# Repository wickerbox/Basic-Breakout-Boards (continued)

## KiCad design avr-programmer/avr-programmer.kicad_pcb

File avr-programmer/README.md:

<!--- start title --->
# Atmega328-based AVR Programmer v1.1
Simple Atmega328-based AVR programmer with ISP and FTDI breakout

Updated: 07 March 2017

Author: Jenner Hanni
Website: http://wickerbox.net
Company: Wickerbox Electronics
License: CERN Open Hardware License v1.2

<!--- end title --->
I made it to have a dedicated board containing Nick Gammon's Arduino sketch for bootloading. 

### Bill of Materials

<!--- bom start --->
|Ref|Qty|Description|Digikey PN|
|---|---|-----------|------|
|C2 C3|2|CAP CER 22pF 100V C0G NP0 0603|399-11145-1-ND|
|C4|1|CAP CER 1UF 25V X7R 0603|587-2984-1-ND|
|C5 C6 C1|3|CAP CER 0.1UF 100V X7R 0603|490-3285-1-ND|
|J1|1|HEADER MALE 6POS TH 1x06 0.1”|952-1902-ND|
|J2|1|HEADER MALE 6POS 2x3 0.1”|952-1921-ND|
|R1|1|RES SMD 10K OHM 5% 1/8W 0805|311-10KARCT-ND|
|S1|1|SWITCH TACTILE SPST-NO 0.05A 12V|SW1020CT-ND|
|S2|1|SWITCH SLIDE SPDT 200MA 30V|EG1903-ND|
|U1|1|IC MCU 8BIT 32KB FLASH 32TQFP|ATMEGA328P-AU-ND|
|X1|1|CRYSTAL 16MHz 18pF 40 OHM 4SMD|CTX1206CT-ND|

<!--- bom end --->

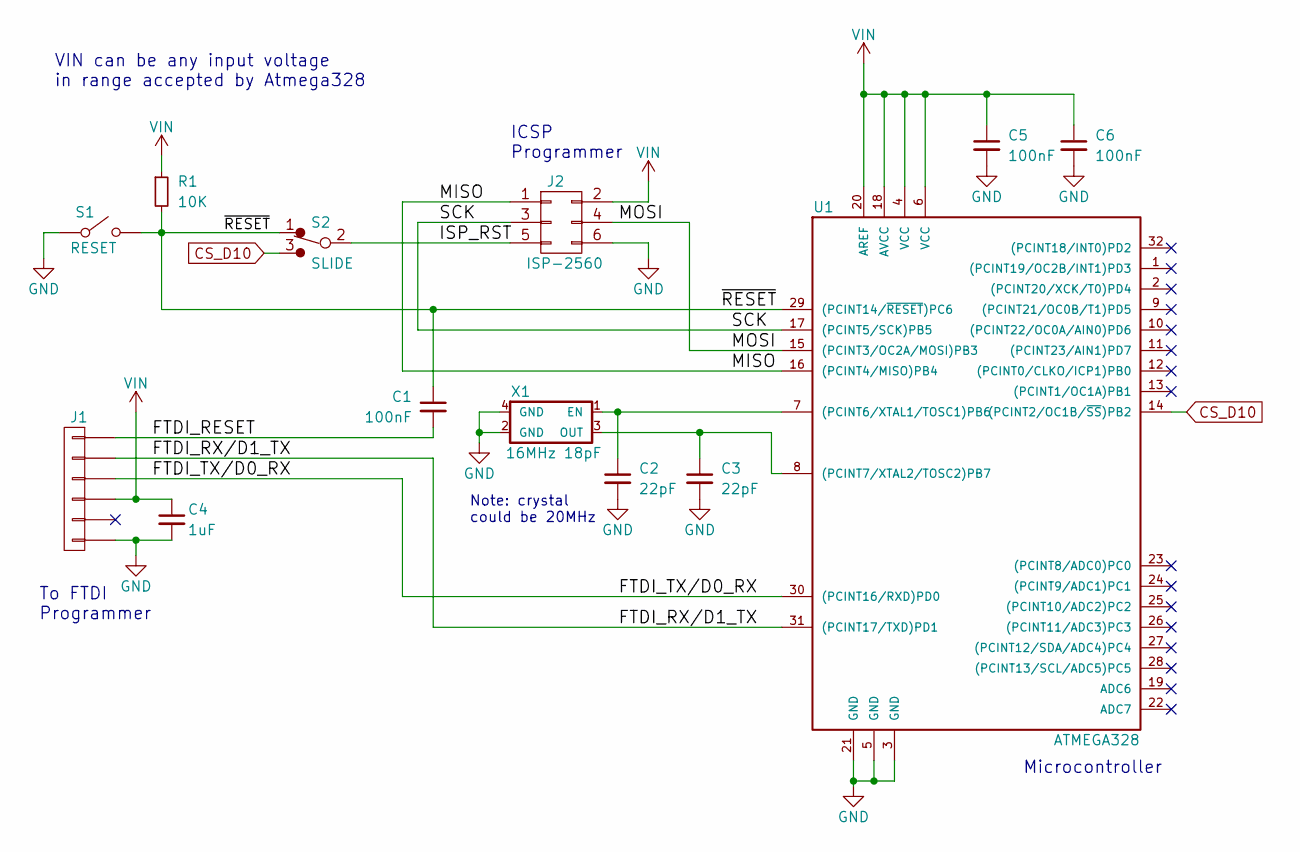
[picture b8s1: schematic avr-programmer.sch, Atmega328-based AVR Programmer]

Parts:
C1, C5, C6: 100nF; RLC-0603-SMD
C2, C3: 22pF; RLC-0603-SMD
C4: 1uF; RLC-0603-SMD
J1: FTDI; CONN-HEADER-STRAIGHT-P2.54MM-1x06
J2: ISP-2560; CONN-HEADER-STRAIGHT-P2.54MM-2x03
R1: 10K; RLC-0805-SMD
S1: RESET; SWITCH-OMRON-MOMENTARY-SMD-B3U-1000P
S2: SLIDE; SWITCH-ESWITCH-SLIDE-TH-EG1218
U1: ATMEGA328; TQFP-32-7x7MM-P0.8MM
X1: 16MHz 18pF; CRYSTAL-CTS-4SMD

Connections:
/FTDI_RESET: C1.2, J1.1
/FTDI_RX/D1_TX: J1.2, U1.31 ((PCINT17/TXD)PD1)
/FTDI_TX/D0_RX: J1.3, U1.30 ((PCINT16/RXD)PD0)
/ISP_RST: J2.5, S2.2
/MISO: J2.1, U1.16 ((PCINT4/MISO)PB4)
/MOSI: J2.4, U1.15 ((PCINT3/OC2A/MOSI)PB3)
/SCK: J2.3, U1.17 ((PCINT5/SCK)PB5)
/~RESET: C1.1, R1.2, S1.2, S2.1, U1.29 ((PCINT14/~RESET~)PC6)
CS_D10: S2.3, U1.14 ((PCINT2/OC1B/~SS~)PB2)
GND: C2.2, C3.2, C4.2, C5.2, C6.2, J1.6, J2.6, S1.1, U1.3 (GND), U1.5 (GND), U1.21 (GND), X1.2 (GND), X1.4 (GND)
unnamed: C2.1, U1.7 ((PCINT6/XTAL1/TOSC1)PB6), X1.1 (EN)
unnamed: C3.1, U1.8 ((PCINT7/XTAL2/TOSC2)PB7), X1.3 (OUT)
VIN: C4.1, C5.1, C6.1, J1.4, J2.2, R1.1, U1.4 (VCC), U1.6 (VCC), U1.18 (AVCC), U1.20 (AREF)

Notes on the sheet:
To FTDI Programmer
ICSP Programmer
VIN can be any input voltage in range accepted by Atmega328
Microcontroller
Note: crystal could be 20MHz

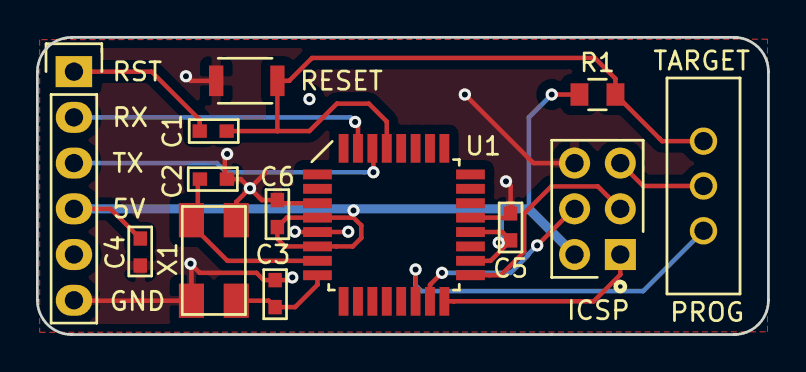
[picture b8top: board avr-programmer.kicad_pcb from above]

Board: 2 copper layers, 40.6 x 16.5 mm, 13 parts (0 on the bottom side), 13 nets.

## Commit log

2016-08-13 Needs major fixes, since board on order doesn't match this after libs update. BOM's OK though.
2016-08-13 Swapped for cheaper capacitors. Updated qty.
2016-08-13 Added project. NOT READY FOR RELEASE. Needed BOM.
2016-08-13 File got screwed up when footprints were adjusted, fixed it up. Gerbers reflect the actual board.
2016-08-13 Working on digital I/O pins.
2016-08-30 Added README, MMA7660 breakout, Teensy LC template.
2016-08-30 Added README to MMA7660 board.
2016-09-01 Added Neopixel Breakout v1.0
2016-09-21 Added Atmega328 v1.1 to fix Tx/Rx and add breakout pins.
2016-09-21 Ignore .rpt files.
2016-09-21 Updated MMA7660 images and README.
2016-09-21 Added link to order boards at OSH Park.
2016-09-21 Added assembly diagram, BOM.
2016-09-21 Removed link to Teensy.
2016-09-21 Updated list of proven circuits.
2016-11-23 New amazing script updated all kinds of stuff.
2016-11-30 Created USB Breakout.
2016-12-31 Created new atmega328 project folder.
2016-12-31 Converted atmega328 to new project format.
2016-12-31 Added shunt jumper.
2016-12-31 Released v1.2
2016-12-31 USB for safekeeping. Atmega328 v1.2 release.
2016-12-31 Markdown formatting fix.
2016-12-31 New gerbers, had to fix version silk.
2017-01-01 Updated list of projects.
2017-01-01 Release v1.1 USB Breakout.
2017-01-01 Release v1.1 MMA7660 breakout.
2017-01-01 Github default KiCad .gitignore hides .csv files wtf.
2017-01-01 Cleanup.
2017-01-01 Release v1.0 Neopixel WS2812B.
2017-01-01 Created blank project dirs.
2017-01-01 Update README.
2017-01-01 Added blank Atmega2560 project.
2017-01-01 Added blank MPU6050 project.
2017-01-02 Pre-release v1.0 MPU9250 boards in two modes.
2017-01-02 Updated README to include schematic.
2017-01-04 Release v1.0 Hinged Micro SD Breakout
2017-01-05 Release v1.0 MicroSD Push-Pull Breakout
2017-01-06 lots of pin adds to atmega2560
2017-01-10 Created AVR Programmer v1.0
2017-01-10 Added schematic for FGPMMOPA6H GPS breakout.
2017-01-10 Release FGPMMOPA6H GPS breakout v1.0
2017-01-27 Add schematic.
2017-02-06 Created schematic images. Updated README.
2017-02-07 Release Neopixel v1.1. Fixed swapped pads.
2017-02-07 Added assembled photo of SD card board.
2017-02-07 Fixed OSH Park shared project link.
2017-02-10 Add switch to AVR Programmer v1.1
2017-02-10 Fix OSH Park preview issue.
2017-02-23 Figuring out Rx/Tx mixup
2017-02-24 Fixed TX/RX.
2017-02-24 MicroSD Push-pull verified to work with 3.3V
2017-02-24 Fix wiring. Add assy diagram. v1.1 release.
2017-02-24 Remove .net from .gitignore.
2017-02-24 Ran updated docs output.
2017-03-07 Release v1.1
2017-03-07 Release v1.0
2017-03-07 Basic connections OK. Accel talking.
2017-03-08 MMA7660 Breakout board v1.1 tested. Release.
2017-03-14 Built and verified v1.1.
2017-03-18 Verified build of hinged microSD v1.1
2017-03-18 Fix typo.
2017-03-18 No idea.
2017-07-20 Created bare MCP73871 project.
2017-07-20 Created bare STNS01 project.
2017-07-20 Updated the BOM.
2017-07-20 Regenerated bom and gerbers.
2017-07-20 Create schematic.
2017-07-20 Generate BOM. Initial parts placement.
2017-07-20 Initial schematic, connectors pending placement.
2017-07-20 Release v1.0 MCP73871, needs ordered and tested.
2017-07-20 Updated assembly diagram, regenerated all files v1.0.
2017-07-21 Release v1.0 STNS01 battery breakout, needs tested.
2017-08-05 Release v1.0 ATSAMD21G Breakout
2017-08-05 Saving unsaved file.
2017-08-05 Release v1.0 STLinkV2 SWD Adapter.
2017-08-14 Updating v1.0 with FabNotes file.
2017-08-14 Automating more of the documentation.
